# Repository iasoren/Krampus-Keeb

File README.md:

### Krampus-Keeb
An ortholinear, ergo, monoblock keyboard with some additional enhancements

Inspired by the Krampus, a half-man and half-goat, Bavarian match to Santa Claus, this keyboard is meant to inspire the badly behaved children inside of us all.

This project aims to create an alice-like, monoblock, lily58 inspired keyboard, with a center macro/num-pad, encoders, and LED. I'm also aiming to incorporate in a modular fashion a trackball and macOS compliant TouchID (fingerprint) sensor, that is all connected as its own device through an integrated USB-C based hub.

# Current State:

| State | Status | Issues | ETA |
|-------|--------|--------|-----|
| Schematic| Starting | x | x |
| PCB | next up | x | x |

## Goals
- [ ] Wireless RP2040 support
- [ ] 2x rotary encoder
- [ ] 1x Side encoder
- [ ] RGB Underglow
- [ ] Key backlight
- [ ] PCB Artwork
- [ ] Fingerprint reader for mac
- [ ] Trackball support
- [ ] Firmware
- [ ] Acrylic case
- [ ] Wooden/metal/acrylic mixed case

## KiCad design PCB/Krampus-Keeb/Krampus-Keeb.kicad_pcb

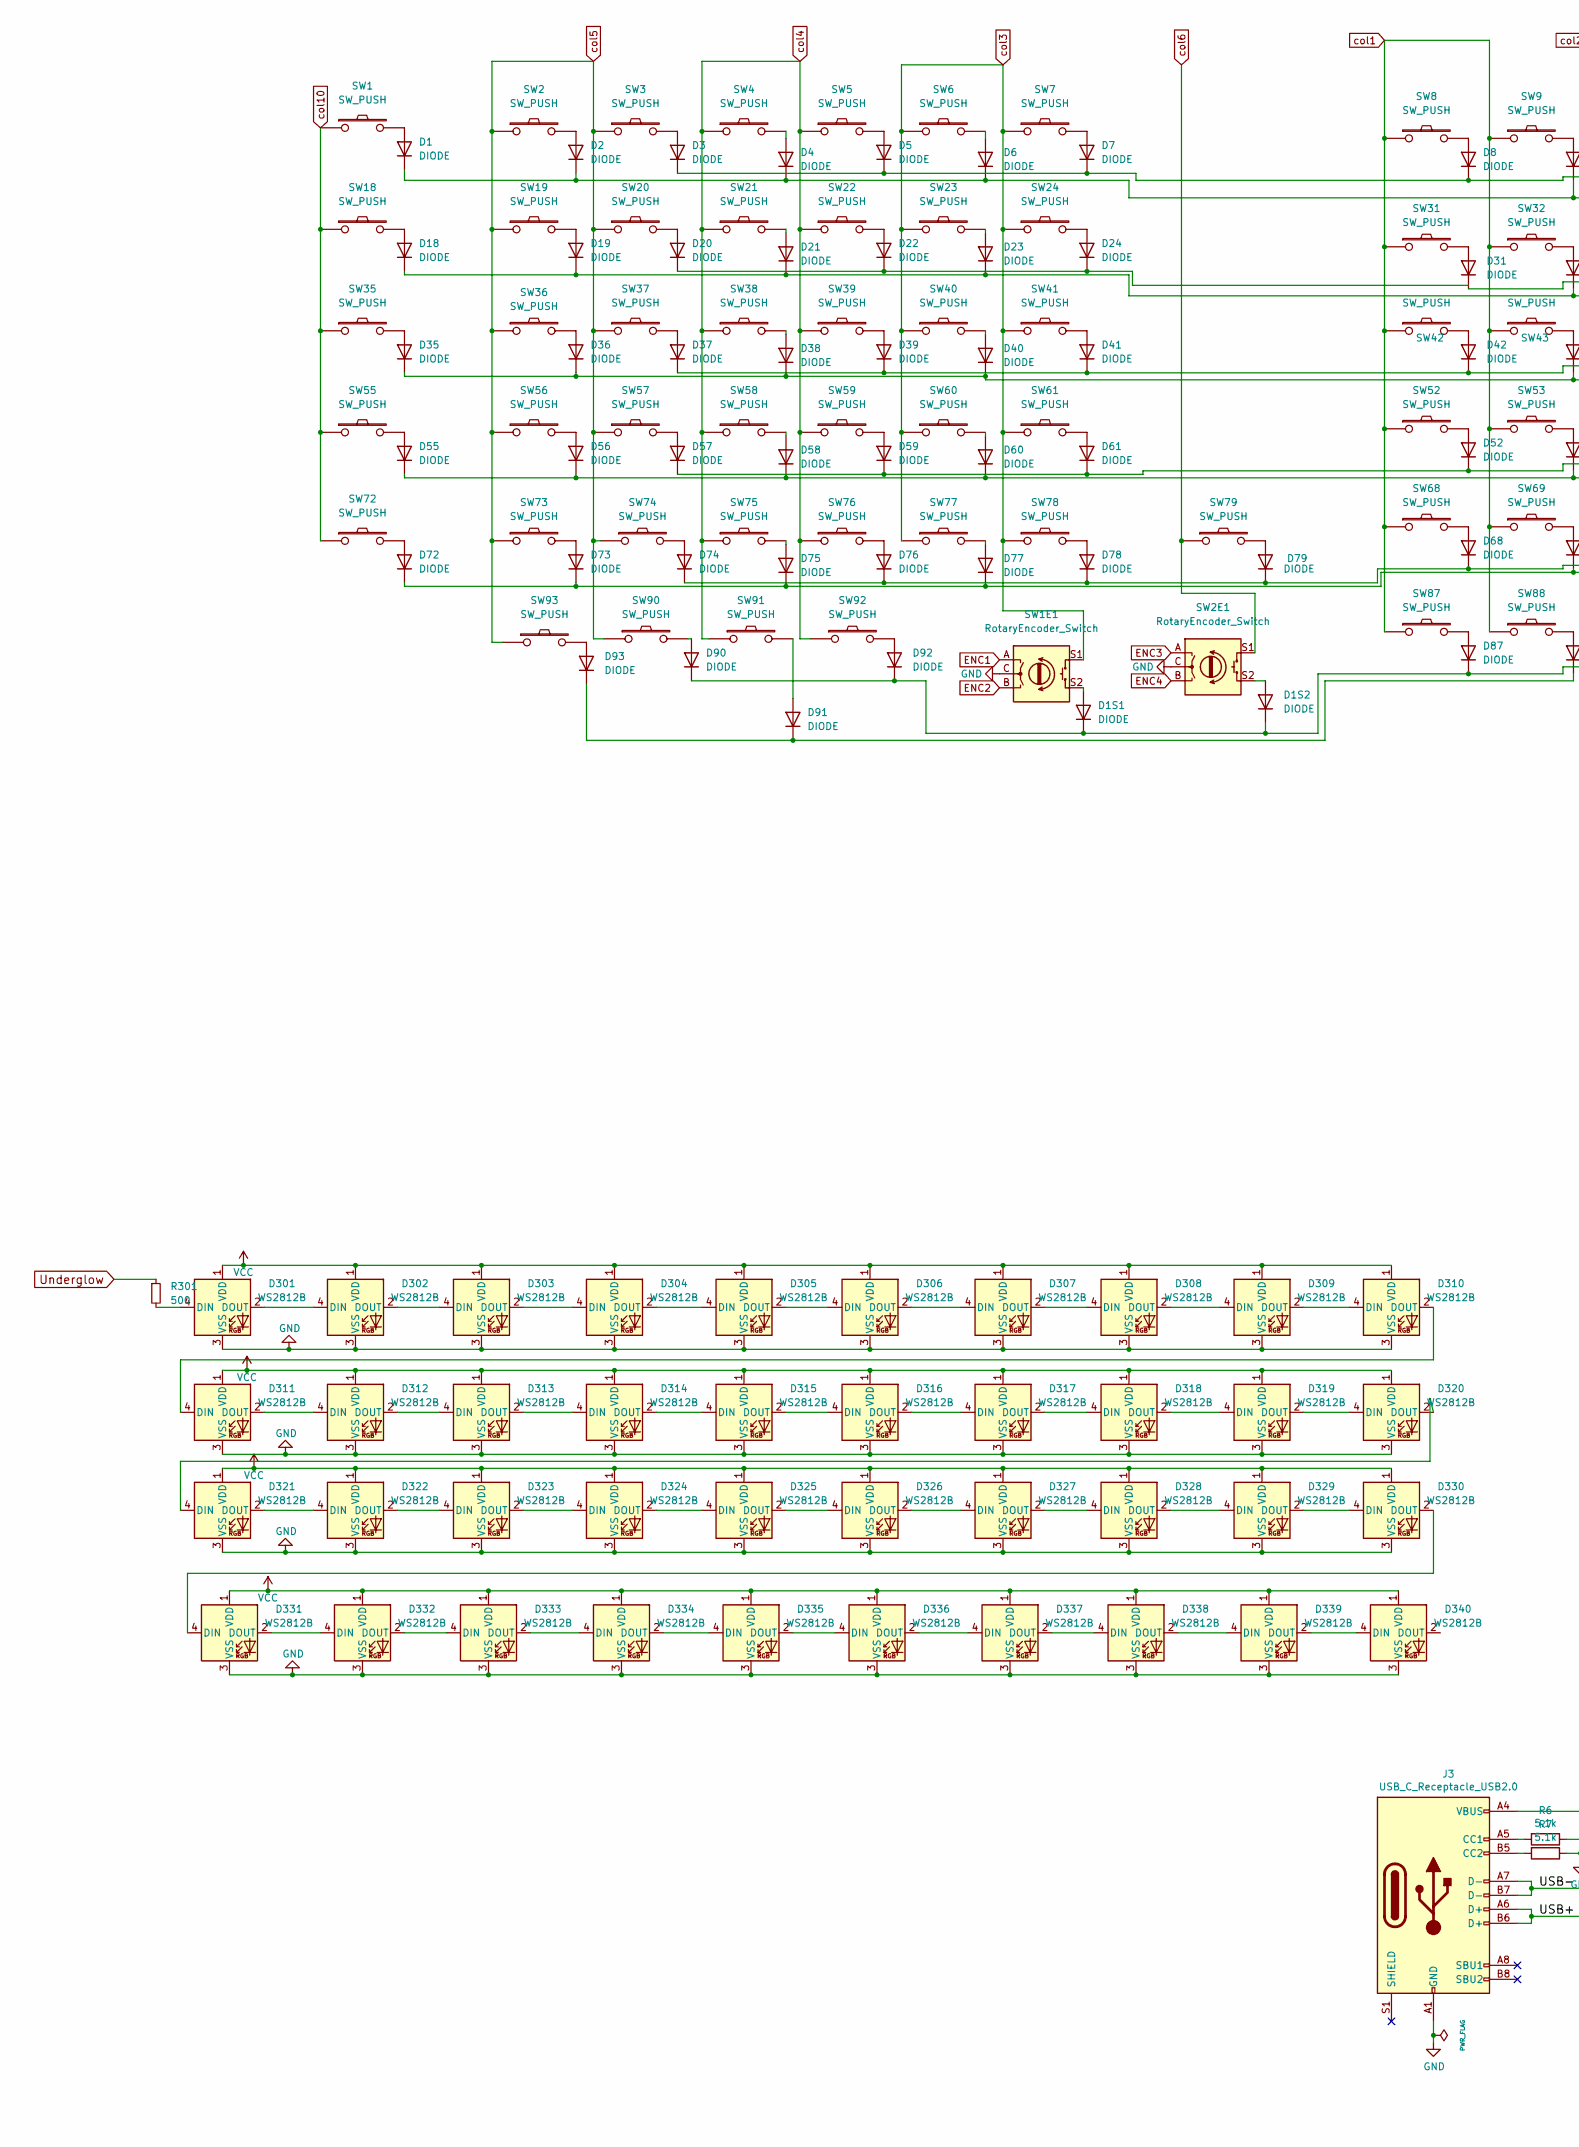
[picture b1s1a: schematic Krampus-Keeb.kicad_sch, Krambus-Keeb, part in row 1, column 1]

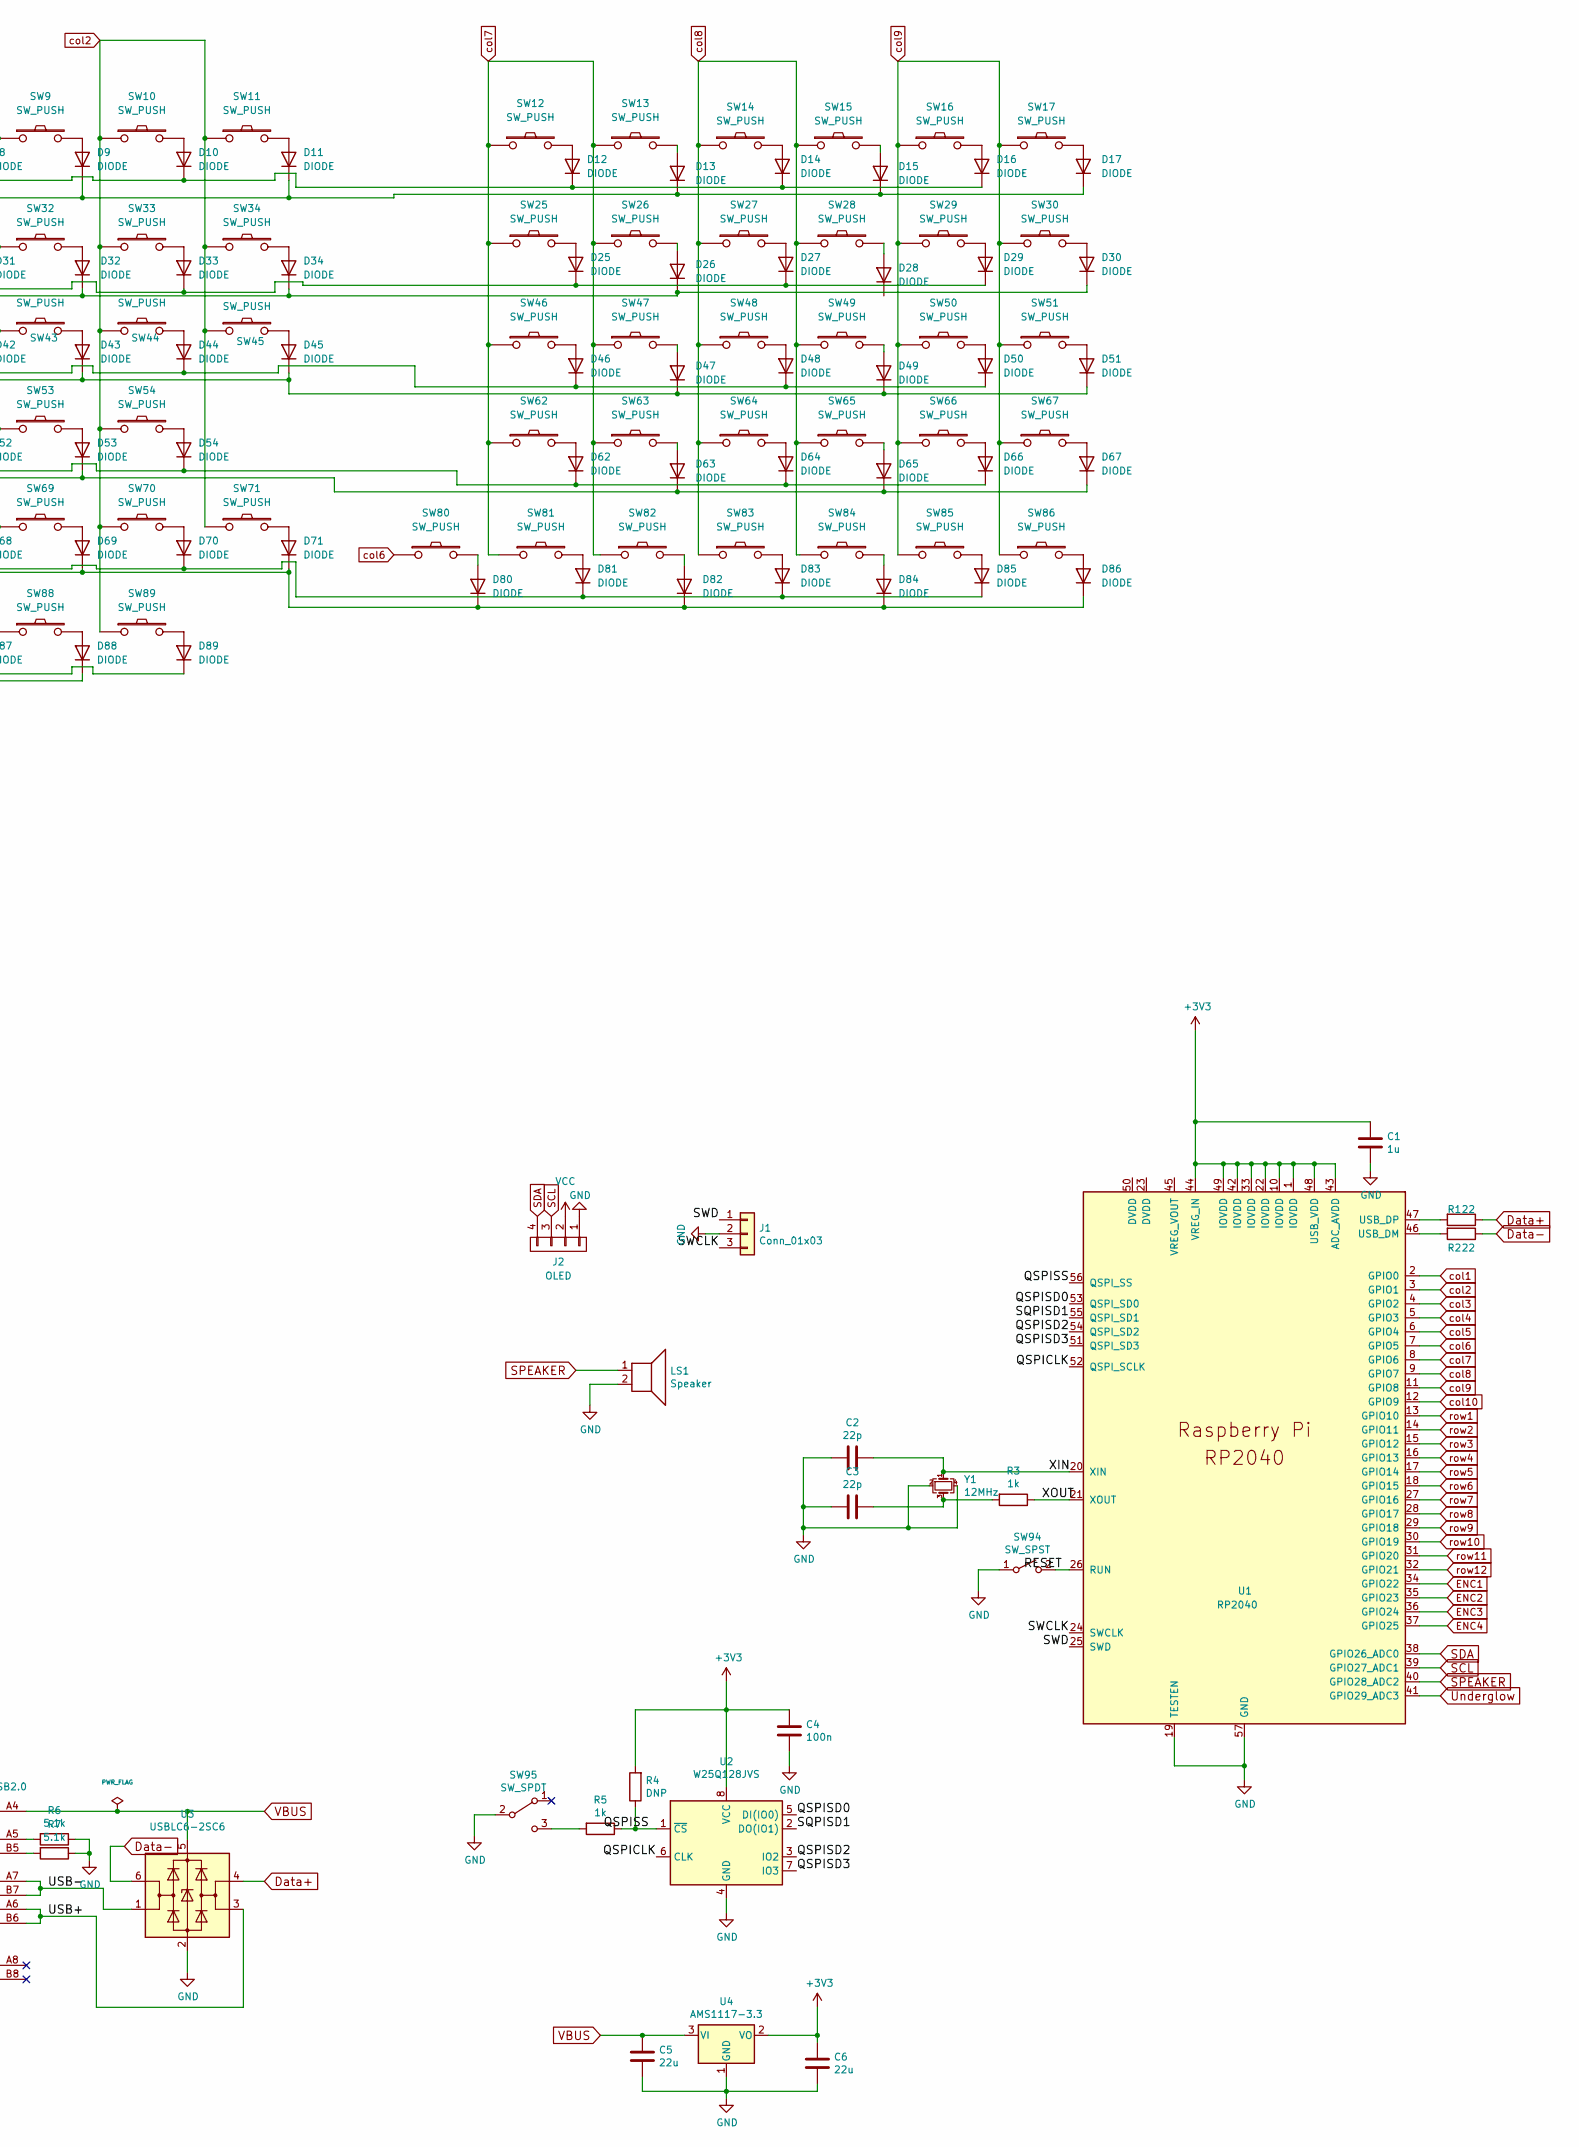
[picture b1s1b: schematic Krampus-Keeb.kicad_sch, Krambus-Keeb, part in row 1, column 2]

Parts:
C1: 1u; C_0603_1608Metric; LCSC C15849
C2, C3: 22p; C_0603_1608Metric; LCSC C1653
C4: 100n; C_0603_1608Metric; LCSC C14663
C5, C6: 22u; C_0603_1608Metric; LCSC C59461
D1, D1S1, D1S2, D2, D3, D4, D5, D6, D7, D8, D9, D10, D11, D12, D13, D14, D15, D16, D17, D18, D19, D20, D21, D22, D23, D24, D25, D26, D27, D28, D29, D30, D31, D32, D33, D34, D35, D36, D37, D38, D39, D40, D41, D42, D43, D44, D45, D46, D47, D48, D49, D50, D51, D52, D53, D54, D55, D56, D57, D58, D59, D60, D61, D62, D63, D64, D65, D66, D67, D68, D69, D70, D71, D72, D73, D74, D75, D76, D77, D78, D79, D80, D81, D82, D83, D84, D85, D86, D87, D88, D89, D90, D91, D92, D93: DIODE; Diode-hybrid-3pad
D301, D302, D303, D304, D305, D306, D307, D308, D309, D310, D311, D312, D313, D314, D315, D316, D317, D318, D319, D320, D321, D322, D323, D324, D325, D326, D327, D328, D329, D330, D331, D332, D333, D334, D335, D336, D337, D338, D339, D340: WS2812B; LED_WS2812B_PLCC4_5.0x5.0mm_P3.2mm
J1: Conn_01x03; PinHeader_1x03_P2.54mm_Vertical
J2: OLED; OLED_4Pin
J3: USB_C_Receptacle_USB2.0; USB_C_Receptacle_HRO_TYPE-C-31-M-12
LS1: Speaker; Buzzer_Mallory_AST1109MLTRQ
R1, R2: 22; R_0603_1608Metric; LCSC C23345
R3, R5: 1k; R_0603_1608Metric; LCSC C21190
R4: DNP; R_0603_1608Metric
R6, R7: 5.1k; R_0603_1608Metric; LCSC C23186
R301: 500; RESISTOR
SW1, SW2, SW3, SW4, SW5, SW6, SW7, SW8, SW9, SW10, SW11, SW12, SW13, SW14, SW15, SW16, SW17, SW18, SW19, SW20, SW21, SW22, SW23, SW24, SW25, SW26, SW27, SW28, SW29, SW30, SW31, SW32, SW33, SW34, SW35, SW36, SW37, SW38, SW39, SW40, SW41, SW42, SW43, SW44, SW45, SW46, SW47, SW48, SW49, SW50, SW51, SW52, SW53, SW54, SW55, SW56, SW57, SW58, SW59, SW60, SW61, SW62, SW63, SW64, SW65, SW66, SW67, SW68, SW69, SW70, SW71, SW72, SW73, SW74, SW75, SW76, SW77, SW78, SW79, SW80, SW81, SW82, SW83, SW84, SW85, SW86, SW87, SW88, SW89, SW90, SW91, SW92, SW93: SW_PUSH; MX_Socket_18mm
SW1E1: RotaryEncoder_Switch; RotaryEncoder_EC11
SW2E1: RotaryEncoder_Switch; RotaryEncoder_EC11B-Horizontal-Dual
SW94: SW_SPST; SW_Push_SPST_NO_Alps_SKRK
SW95: SW_SPDT; SW_SPDT_PCM12
U1: RP2040; RP2040-QFN-56
U2: W25Q128JVS; SOIC-8_5.23x5.23mm_P1.27mm; LCSC C97521
U3: USBLC6-2SC6; SOT-23-6; LCSC C558442
U4: AMS1117-3.3; SOT-223-3_TabPin2; LCSC C6186
Y1: 12MHz; Crystal_SMD_3225-4Pin_3.2x2.5mm; LCSC C93114

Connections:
+3V3: C1.1, C4.1, C6.1, R4.2, U1.1 (IOVDD), U1.10 (IOVDD), U1.22 (IOVDD), U1.33 (IOVDD), U1.42 (IOVDD), U1.43 (ADC_AVDD), U1.44 (VREG_IN), U1.48 (USB_VDD), U1.49 (IOVDD), U2.8 (VCC), U4.2 (VO)
/QSPICLK: U1.52 (QSPI_SCLK), U2.6 (CLK)
/QSPISD0: U1.53 (QSPI_SD0), U2.5 (DI(IO0))
/QSPISD2: U1.54 (QSPI_SD2), U2.3 (IO2)
/QSPISD3: U1.51 (QSPI_SD3), U2.7 (IO3)
/QSPISS: R4.1, R5.1, U1.56 (QSPI_SS), U2.1 (~CS)
/RESET: SW94.2 (B), U1.26 (RUN)
/SQPISD1: U1.55 (QSPI_SD1), U2.2 (DO(IO1))
/SWCLK: J1.3, U1.24 (SWCLK)
/SWD: J1.1, U1.25 (SWD)
/USB+: J3.A6 (D+), J3.B6 (D+), U3.3 (I/O2)
/USB-: J3.A7 (D-), J3.B7 (D-), U3.1 (I/O1)
/XIN: C2.1, U1.20 (XIN), Y1.1
/XOUT: R3.1, U1.21 (XOUT)
Data+: R1.1, U3.4 (I/O2)
Data-: R2.1, U3.6 (I/O1)
ENC1: SW1E1.A, U1.34 (GPIO22)
ENC2: SW1E1.B, U1.35 (GPIO23)
ENC3: SW2E1.A, U1.36 (GPIO24)
ENC4: SW2E1.B, U1.37 (GPIO25)
GND: C1.2, C2.2, C3.2, C4.2, C5.2, C6.2, D301.3 (VSS), D302.3 (VSS), D303.3 (VSS), D304.3 (VSS), D305.3 (VSS), D306.3 (VSS), D307.3 (VSS), D308.3 (VSS), D309.3 (VSS), D310.3 (VSS), D311.3 (VSS), D312.3 (VSS), D313.3 (VSS), D314.3 (VSS), D315.3 (VSS), D316.3 (VSS), D317.3 (VSS), D318.3 (VSS), D319.3 (VSS), D320.3 (VSS), D321.3 (VSS), D322.3 (VSS), D323.3 (VSS), D324.3 (VSS), D325.3 (VSS), D326.3 (VSS), D327.3 (VSS), D328.3 (VSS), D329.3 (VSS), D330.3 (VSS), D331.3 (VSS), D332.3 (VSS), D333.3 (VSS), D334.3 (VSS), D335.3 (VSS), D336.3 (VSS), D337.3 (VSS), D338.3 (VSS), D339.3 (VSS), D340.3 (VSS), J1.2, J2.1, J3.A1 (GND), J3.A12 (GND), J3.B1 (GND), J3.B12 (GND), LS1.2, R6.1, R7.1, SW1E1.C, SW2E1.C, SW94.1 (A), SW95.2 (B), U1.19 (TESTEN), U1.57 (GND), U2.4 (GND), U3.2 (GND), U4.1 (GND), Y1.2, Y1.4
unnamed: C3.1, R3.2, Y1.3
unnamed: D1.1 (A), SW1.2
unnamed: D1.2 (K), D2.2 (K), D4.2 (K), D6.2 (K), D9.2 (K), D11.2 (K), D13.2 (K), D15.2 (K), D17.2 (K)
unnamed: D1S1.1 (A), SW1E1.S2
unnamed: D1S1.2 (K), D1S2.2 (K), D87.2 (K), D89.2 (K), D90.2 (K), D92.2 (K)
unnamed: D1S2.1 (A), SW2E1.S2
unnamed: D2.1 (A), SW2.2
unnamed: D3.1 (A), SW3.2
unnamed: D4.1 (A), SW4.2
unnamed: D5.1 (A), SW5.2
unnamed: D6.1 (A), SW6.2
unnamed: D7.1 (A), SW7.2
unnamed: D8.1 (A), SW8.2
unnamed: D9.1 (A), SW9.2
unnamed: D10.1 (A), SW10.2
unnamed: D3.2 (K), D5.2 (K), D7.2 (K), D8.2 (K), D10.2 (K), D12.2 (K), D14.2 (K), D16.2 (K)
unnamed: D11.1 (A), SW11.2
unnamed: D12.1 (A), SW12.2
unnamed: D13.1 (A), SW13.2
unnamed: D14.1 (A), SW14.2
unnamed: D15.1 (A), SW15.2
unnamed: D16.1 (A), SW16.2
unnamed: D17.1 (A), SW17.2
unnamed: D18.1 (A), SW18.2
unnamed: D18.2 (K), D19.2 (K), D21.2 (K), D23.2 (K), D26.2 (K), D30.2 (K), D32.2 (K), D34.2 (K)
unnamed: D19.1 (A), SW19.2
unnamed: D20.1 (A), SW20.2
unnamed: D20.2 (K), D22.2 (K), D24.2 (K)
unnamed: D21.1 (A), SW21.2
unnamed: D22.1 (A), SW22.2
unnamed: D23.1 (A), SW23.2
unnamed: D24.1 (A), SW24.2
unnamed: D25.1 (A), SW25.2
unnamed: D25.2 (K), D27.2 (K), D29.2 (K), D31.2 (K), D33.2 (K)
unnamed: D26.1 (A), SW26.2
unnamed: D27.1 (A), SW27.2
unnamed: D28.1 (A), SW28.2
unnamed: D29.1 (A), SW29.2
unnamed: D30.1 (A), SW30.2
unnamed: D31.1 (A), SW31.2
unnamed: D32.1 (A), SW32.2
unnamed: D33.1 (A), SW33.2
unnamed: D34.1 (A), SW34.2
unnamed: D35.1 (A), SW35.2
unnamed: D35.2 (K), D36.2 (K), D38.2 (K), D40.2 (K), D43.2 (K), D45.2 (K), D47.2 (K), D49.2 (K), D51.2 (K)
unnamed: D36.1 (A), SW36.2
unnamed: D37.1 (A), SW37.2
unnamed: D37.2 (K), D39.2 (K), D41.2 (K), D42.2 (K), D44.2 (K), D46.2 (K), D48.2 (K), D50.2 (K)
unnamed: D38.1 (A), SW38.2
unnamed: D39.1 (A), SW39.2
unnamed: D40.1 (A), SW40.2
unnamed: D41.1 (A), SW41.2
unnamed: D42.1 (A), SW42.2
unnamed: D43.1 (A), SW43.2
unnamed: D44.1 (A), SW44.2
unnamed: D45.1 (A), SW45.2
unnamed: D46.1 (A), SW46.2
unnamed: D47.1 (A), SW47.2
unnamed: D48.1 (A), SW48.2
unnamed: D49.1 (A), SW49.2
unnamed: D50.1 (A), SW50.2
unnamed: D51.1 (A), SW51.2
unnamed: D52.1 (A), SW52.2
unnamed: D52.2 (K), D54.2 (K), D57.2 (K), D59.2 (K), D61.2 (K), D62.2 (K), D64.2 (K), D66.2 (K)
unnamed: D53.1 (A), SW53.2
unnamed: D53.2 (K), D55.2 (K), D56.2 (K), D58.2 (K), D60.2 (K), D63.2 (K), D65.2 (K), D67.2 (K)
unnamed: D54.1 (A), SW54.2
unnamed: D55.1 (A), SW55.2
unnamed: D56.1 (A), SW56.2
unnamed: D57.1 (A), SW57.2
unnamed: D58.1 (A), SW58.2
unnamed: D59.1 (A), SW59.2
unnamed: D60.1 (A), SW60.2
unnamed: D61.1 (A), SW61.2
unnamed: D62.1 (A), SW62.2
unnamed: D63.1 (A), SW63.2
unnamed: D64.1 (A), SW64.2
unnamed: D65.1 (A), SW65.2
unnamed: D66.1 (A), SW66.2
unnamed: D67.1 (A), SW67.2
unnamed: D68.1 (A), SW68.2
unnamed: D68.2 (K), D70.2 (K), D74.2 (K), D76.2 (K), D78.2 (K), D79.2 (K), D81.2 (K), D83.2 (K), D85.2 (K)
unnamed: D69.1 (A), SW69.2
unnamed: D69.2 (K), D71.2 (K), D72.2 (K), D73.2 (K), D75.2 (K), D77.2 (K), D80.2 (K), D82.2 (K), D84.2 (K), D86.2 (K)
unnamed: D70.1 (A), SW70.2
unnamed: D71.1 (A), SW71.2
unnamed: D72.1 (A), SW72.2
unnamed: D73.1 (A), SW73.2
unnamed: D74.1 (A), SW74.2
unnamed: D75.1 (A), SW75.2
unnamed: D76.1 (A), SW76.2
unnamed: D77.1 (A), SW77.2
unnamed: D78.1 (A), SW78.2
unnamed: D79.1 (A), SW79.2
unnamed: D80.1 (A), SW80.2
unnamed: D81.1 (A), SW81.2
unnamed: D82.1 (A), SW82.2
unnamed: D83.1 (A), SW83.2
unnamed: D84.1 (A), SW84.2
unnamed: D85.1 (A), SW85.2
unnamed: D86.1 (A), SW86.2
unnamed: D87.1 (A), SW87.2
unnamed: D88.1 (A), SW88.2
unnamed: D88.2 (K), D91.2 (K), D93.2 (K)
unnamed: D89.1 (A), SW89.2
unnamed: D90.1 (A), SW90.2
unnamed: D91.1 (A), SW91.2
unnamed: D92.1 (A), SW92.2
unnamed: D93.1 (A), SW93.2
unnamed: D301.2 (DOUT), D302.4 (DIN)
unnamed: D301.4 (DIN), R301.2
unnamed: D302.2 (DOUT), D303.4 (DIN)
unnamed: D303.2 (DOUT), D304.4 (DIN)
unnamed: D304.2 (DOUT), D305.4 (DIN)
unnamed: D305.2 (DOUT), D306.4 (DIN)
unnamed: D306.2 (DOUT), D307.4 (DIN)
unnamed: D307.2 (DOUT), D308.4 (DIN)
unnamed: D308.2 (DOUT), D309.4 (DIN)
unnamed: D309.2 (DOUT), D310.4 (DIN)
unnamed: D310.2 (DOUT), D311.4 (DIN)
unnamed: D311.2 (DOUT), D312.4 (DIN)
unnamed: D312.2 (DOUT), D313.4 (DIN)
unnamed: D313.2 (DOUT), D314.4 (DIN)
unnamed: D314.2 (DOUT), D315.4 (DIN)
unnamed: D315.2 (DOUT), D316.4 (DIN)
unnamed: D316.2 (DOUT), D317.4 (DIN)
unnamed: D317.2 (DOUT), D318.4 (DIN)
unnamed: D318.2 (DOUT), D319.4 (DIN)
unnamed: D319.2 (DOUT), D320.4 (DIN)
unnamed: D320.2 (DOUT), D321.4 (DIN)
unnamed: D321.2 (DOUT), D322.4 (DIN)
unnamed: D322.2 (DOUT), D323.4 (DIN)
unnamed: D323.2 (DOUT), D324.4 (DIN)
unnamed: D324.2 (DOUT), D325.4 (DIN)
unnamed: D325.2 (DOUT), D326.4 (DIN)
unnamed: D326.2 (DOUT), D327.4 (DIN)
unnamed: D327.2 (DOUT), D328.4 (DIN)
unnamed: D328.2 (DOUT), D329.4 (DIN)
unnamed: D329.2 (DOUT), D330.4 (DIN)
unnamed: D330.2 (DOUT), D331.4 (DIN)
unnamed: D331.2 (DOUT), D332.4 (DIN)
unnamed: D332.2 (DOUT), D333.4 (DIN)
unnamed: D333.2 (DOUT), D334.4 (DIN)
unnamed: D334.2 (DOUT), D335.4 (DIN)
unnamed: D335.2 (DOUT), D336.4 (DIN)
unnamed: D336.2 (DOUT), D337.4 (DIN)
unnamed: D337.2 (DOUT), D338.4 (DIN)
unnamed: D338.2 (DOUT), D339.4 (DIN)
unnamed: D339.2 (DOUT), D340.4 (DIN)
unnamed: J3.A5 (CC1), R6.2
unnamed: J3.B5 (CC2), R7.2
unnamed: R1.2, U1.47 (USB_DP)
unnamed: R2.2, U1.46 (USB_DM)
unnamed: R5.2, SW95.3 (C)
SCL: J2.3, U1.39 (GPIO27_ADC1)
SDA: J2.4, U1.38 (GPIO26_ADC0)
SPEAKER: LS1.1, U1.40 (GPIO28_ADC2)
Underglow: R301.1, U1.41 (GPIO29_ADC3)
VBUS: C5.1, J3.A4 (VBUS), J3.A9 (VBUS), J3.B4 (VBUS), J3.B9 (VBUS), U3.5 (VBUS), U4.3 (VI)
VCC: D301.1 (VDD), D302.1 (VDD), D303.1 (VDD), D304.1 (VDD), D305.1 (VDD), D306.1 (VDD), D307.1 (VDD), D308.1 (VDD), D309.1 (VDD), D310.1 (VDD), D311.1 (VDD), D312.1 (VDD), D313.1 (VDD), D314.1 (VDD), D315.1 (VDD), D316.1 (VDD), D317.1 (VDD), D318.1 (VDD), D319.1 (VDD), D320.1 (VDD), D321.1 (VDD), D322.1 (VDD), D323.1 (VDD), D324.1 (VDD), D325.1 (VDD), D326.1 (VDD), D327.1 (VDD), D328.1 (VDD), D329.1 (VDD), D330.1 (VDD), D331.1 (VDD), D332.1 (VDD), D333.1 (VDD), D334.1 (VDD), D335.1 (VDD), D336.1 (VDD), D337.1 (VDD), D338.1 (VDD), D339.1 (VDD), D340.1 (VDD), J2.2
col1: SW8.1, SW9.1, SW31.1, SW32.1, SW42.1, SW43.1, SW52.1, SW53.1, SW68.1, SW69.1, SW87.1, SW88.1, U1.2 (GPIO0)
col2: SW10.1, SW11.1, SW33.1, SW34.1, SW44.1, SW45.1, SW54.1, SW70.1, SW71.1, SW89.1, U1.3 (GPIO1)
col3: SW1E1.S1, SW6.1, SW7.1, SW23.1, SW24.1, SW40.1, SW41.1, SW60.1, SW61.1, SW77.1, SW78.1, U1.4 (GPIO2)
col4: SW4.1, SW5.1, SW21.1, SW22.1, SW38.1, SW39.1, SW58.1, SW59.1, SW75.1, SW76.1, SW91.1, SW92.1, U1.5 (GPIO3)
col5: SW2.1, SW3.1, SW19.1, SW20.1, SW36.1, SW37.1, SW56.1, SW57.1, SW73.1, SW74.1, SW90.1, SW93.1, U1.6 (GPIO4)
col6: SW2E1.S1, SW79.1, SW80.1, U1.7 (GPIO5)
col7: SW12.1, SW13.1, SW25.1, SW26.1, SW46.1, SW47.1, SW62.1, SW63.1, SW81.1, SW82.1, U1.8 (GPIO6)
col8: SW14.1, SW15.1, SW27.1, SW28.1, SW48.1, SW49.1, SW64.1, SW65.1, SW83.1, SW84.1, U1.9 (GPIO7)
col9: SW16.1, SW17.1, SW29.1, SW30.1, SW50.1, SW51.1, SW66.1, SW67.1, SW85.1, SW86.1, U1.11 (GPIO8)
col10: SW1.1, SW18.1, SW35.1, SW55.1, SW72.1, U1.12 (GPIO9)
row1: U1.13 (GPIO10)
row2: U1.14 (GPIO11)
row3: U1.15 (GPIO12)
row4: U1.16 (GPIO13)
row5: U1.17 (GPIO14)
row6: U1.18 (GPIO15)
row7: U1.27 (GPIO16)
row8: U1.28 (GPIO17)
row9: U1.29 (GPIO18)
row10: U1.30 (GPIO19)
row11: U1.31 (GPIO20)
row12: U1.32 (GPIO21)

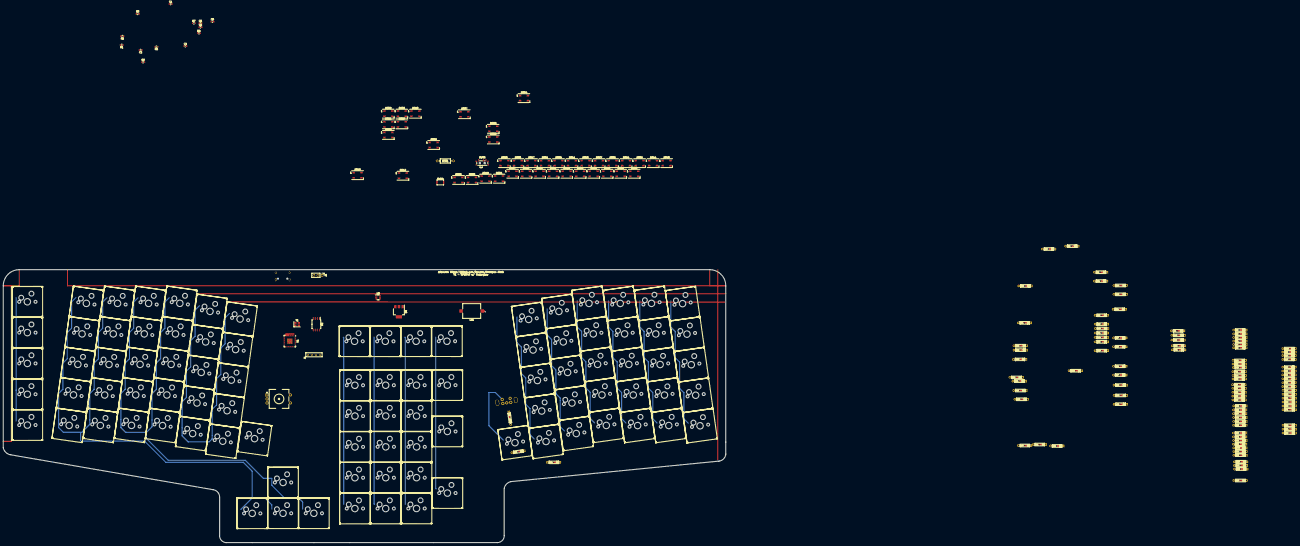
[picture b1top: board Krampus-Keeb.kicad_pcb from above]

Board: 4 copper layers, 450.0 x 170.0 mm, 255 parts (1 on the bottom side), 191 nets.

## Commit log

2023-05-29 Updates
    Schematic updates and some PCB work
